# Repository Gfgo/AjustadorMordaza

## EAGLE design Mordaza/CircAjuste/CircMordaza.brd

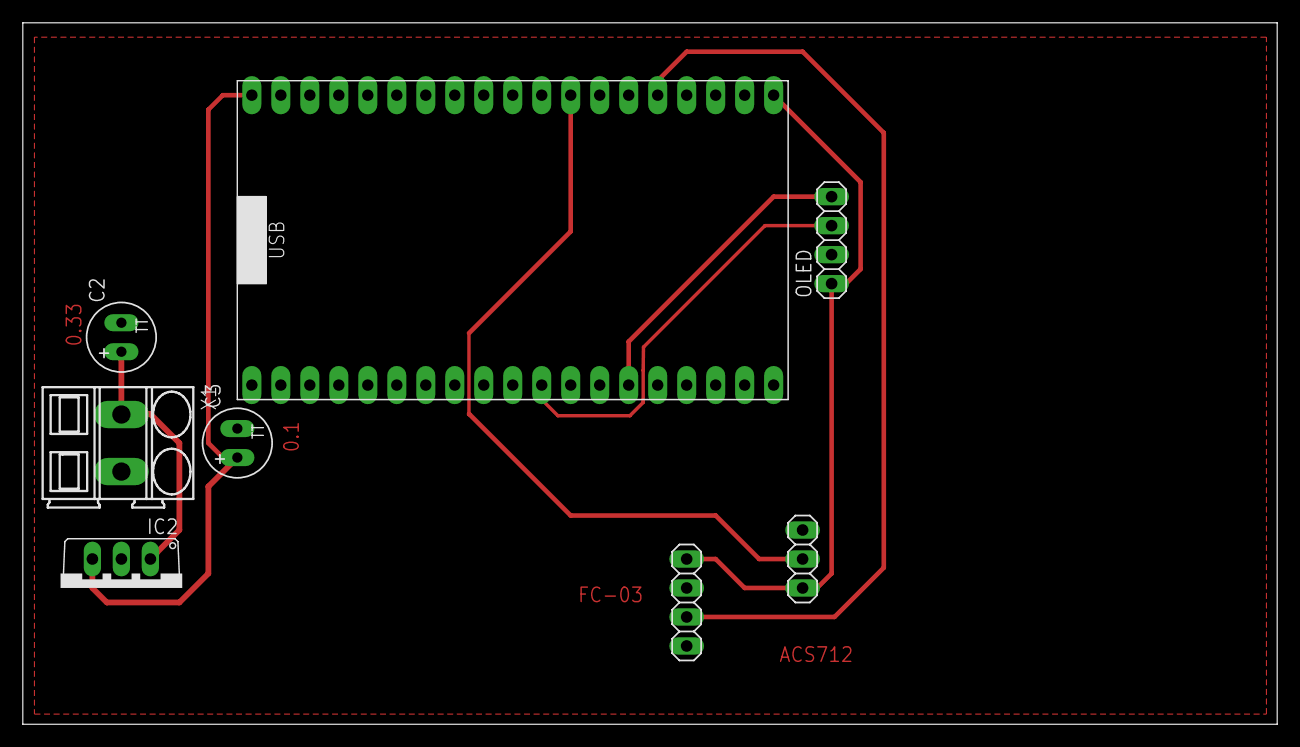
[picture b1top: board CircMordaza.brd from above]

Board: 2 copper layers, 109.9 x 61.5 mm, 8 parts (0 on the bottom side), 8 nets.

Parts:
ACS712: 1X03
C2: 0.33; TT2D6
C3: 0.1; TT2D6
FC-03: 1X04
IC2: 7805TV; TO220V
OLED: 1X04
U$1: ESP32WESP32W; ESP32W
X1: SMKDSP_1,5/2

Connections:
+3V3: ACS712.1, FC-03.1, OLED.1, U$1.3.3V
+5V: C3.+, IC2.3, U$1.5V
+12V: C2.+, IC2.1, X1.1
GND: ACS712.3, C2.-, C3.-, FC-03.2, IC2.2, OLED.2, U$1.GND1, U$1.GND2, U$1.GND3, X1.2
IO33: ACS712.2, U$1.GPIO33
IO34: FC-03.3, U$1.GPIO34
SCK: OLED.3, U$1.GPIO18
SDA: OLED.4, U$1.GPIO21

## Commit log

2022-12-01 Create Mordaza.ino
    Inicio
2022-12-02 rpm funcionando
2022-12-05 Update Mordaza.ino
    adc117+ tacometro ok
2024-05-31 Actualizacion
    Actualizacion rpm ok 31/05/2024
2024-05-31 Update Mordaza.ino
    31/05/2024
    velocidad lineal +corriente+oled ok
2024-06-04 Update Mordaza.ino
    Cambios en pantalla e implementación de medición de torque.
2024-06-05 Update Mordaza.ino
    Actualizar esp
2024-06-11 Update Mordaza.ino
    Esp ok
2024-06-12 12/06
    Actualización circuito 12/06
2024-06-18 Circuito y prog ok 18/06
    Circuito y prog ok 18/06
